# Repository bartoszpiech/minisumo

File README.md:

# minisumo
A minisumo project for my mobile robots classes

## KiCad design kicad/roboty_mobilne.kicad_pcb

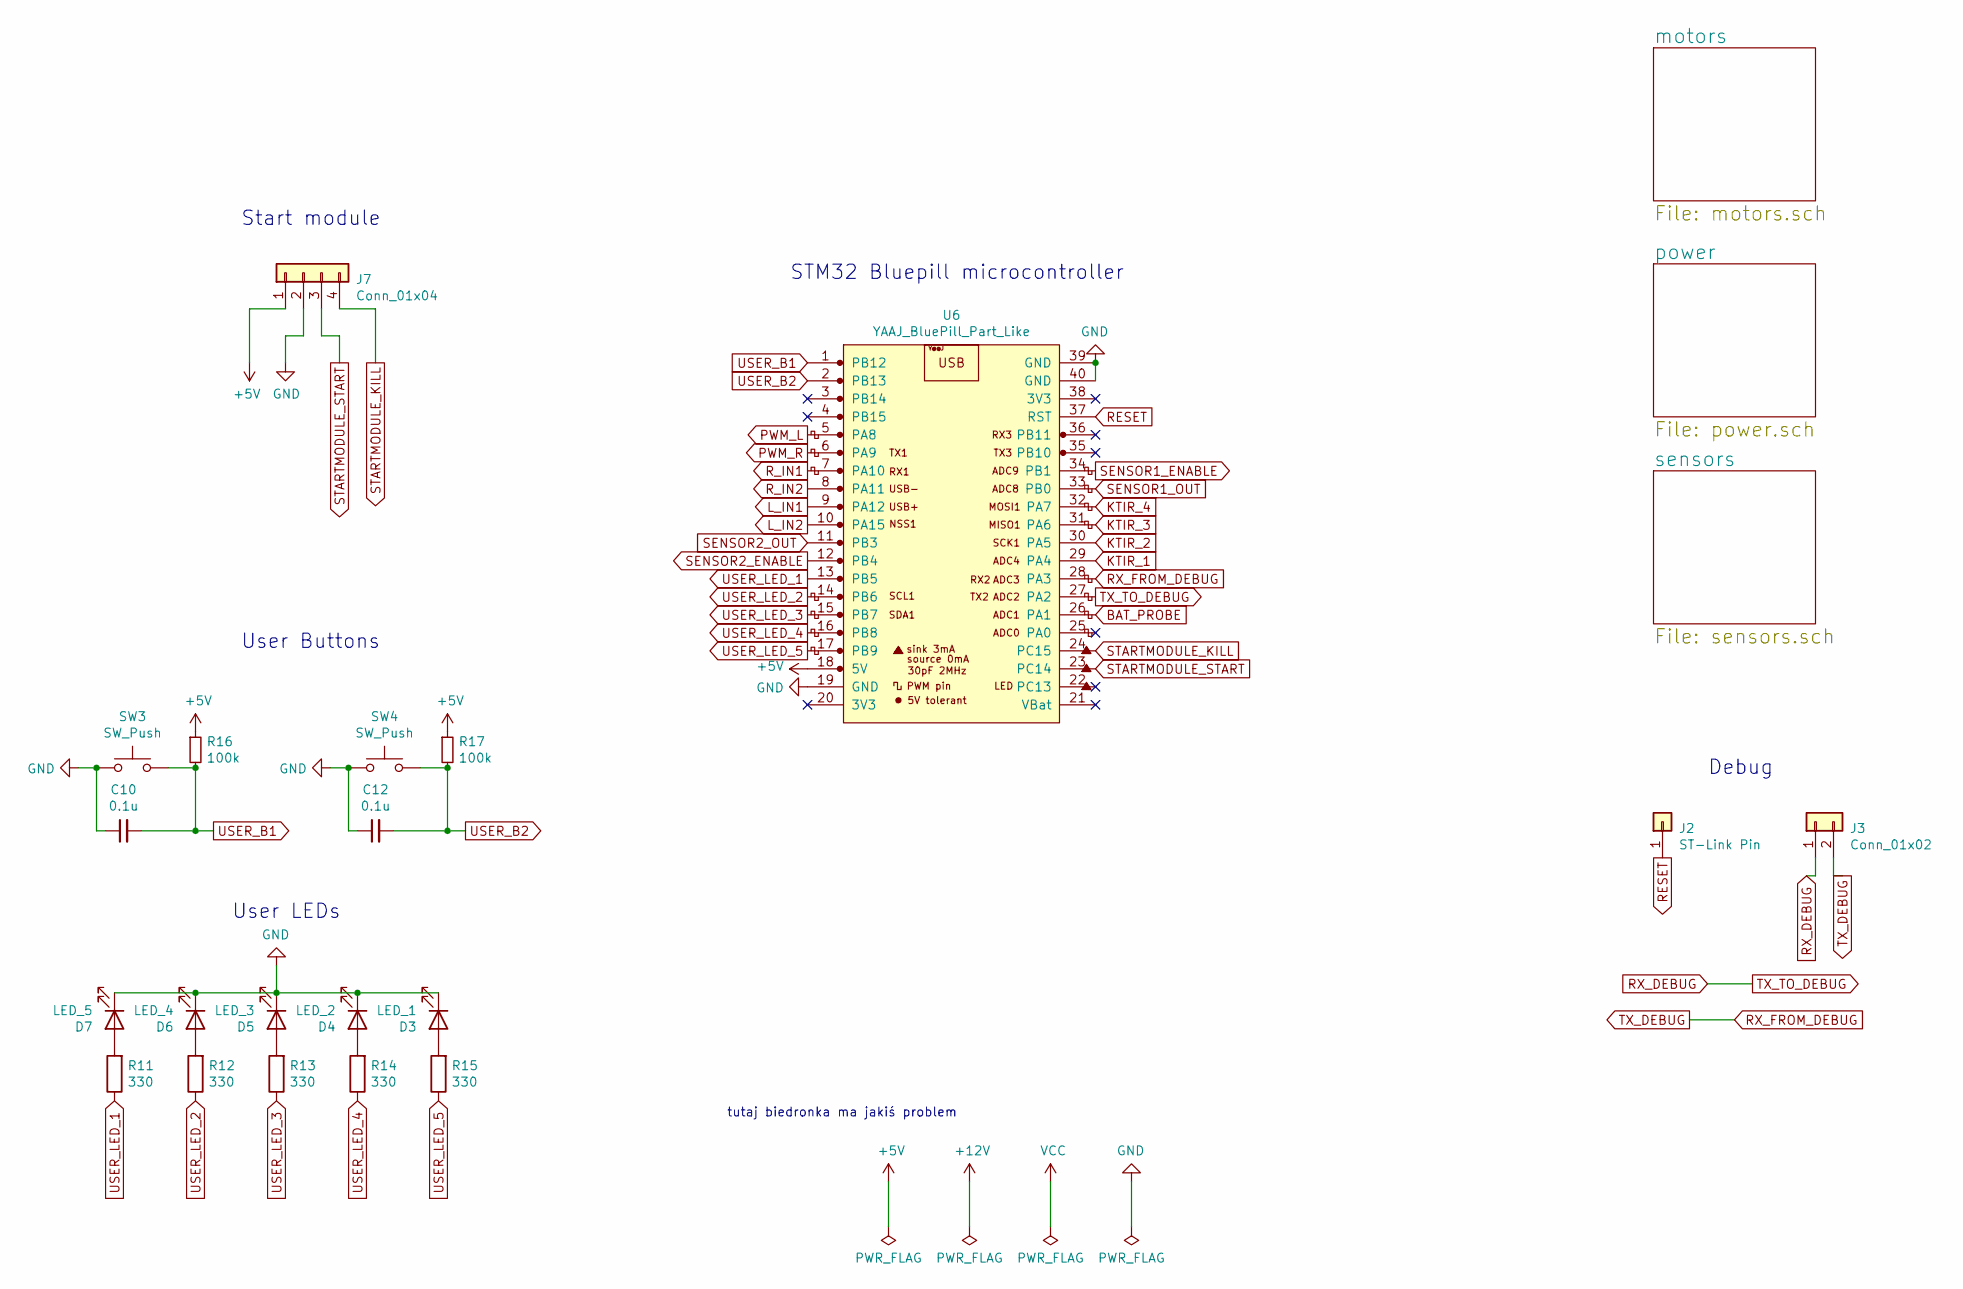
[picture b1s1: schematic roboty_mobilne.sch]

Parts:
C10, C12: 0.1u; C_Disc_D10.5mm_W5.0mm_P7.50mm
D3: LED_1; LED_D5.0mm
D4: LED_2; LED_D5.0mm
D5: LED_3; LED_D5.0mm
D6: LED_4; LED_D5.0mm
D7: LED_5; LED_D5.0mm
J2: ST-Link Pin; PinSocket_1x01_P2.54mm_Vertical
J3: Conn_01x02; PinSocket_1x02_P2.54mm_Vertical
J7: Conn_01x04; PinSocket_1x04_P2.54mm_Vertical
R11, R12, R13, R14, R15: 330; R_1206_3216Metric_Pad1.30x1.75mm_HandSolder
R16, R17: 100k; R_1206_3216Metric_Pad1.30x1.75mm_HandSolder
SW3, SW4: SW_Push; SW_PUSH_6mm_H5mm
U6: YAAJ_BluePill_Part_Like; YAAJ_BluePill_1

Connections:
+5V: J7.1, R16.1, R17.1, U6.18 (5V); also elsewhere on the board
BAT_PROBE: U6.26 (PA1); also elsewhere on the board
GND: C10.1, C12.1, D3.1 (K), D4.1 (K), D5.1 (K), D6.1 (K), D7.1 (K), J7.2, SW3.1, SW4.1, U6.19 (GND), U6.39 (GND), U6.40 (GND); also elsewhere on the board
KTIR_1: U6.29 (PA4); also elsewhere on the board
KTIR_2: U6.30 (PA5); also elsewhere on the board
KTIR_3: U6.31 (PA6); also elsewhere on the board
KTIR_4: U6.32 (PA7); also elsewhere on the board
L_IN1: U6.9 (PA12); also elsewhere on the board
L_IN2: U6.10 (PA15); also elsewhere on the board
unnamed: D3.2 (A), R15.2
unnamed: D4.2 (A), R14.2
unnamed: D5.2 (A), R13.2
unnamed: D6.2 (A), R12.2
unnamed: D7.2 (A), R11.2
PWM_L: U6.5 (PA8); also elsewhere on the board
PWM_R: U6.6 (PA9); also elsewhere on the board
RESET: J2.1, U6.37 (RST)
RX_DEBUG: J3.1, U6.27 (PA2)
RX_FROM_DEBUG: J3.2, U6.28 (PA3)
R_IN1: U6.7 (PA10); also elsewhere on the board
R_IN2: U6.8 (PA11); also elsewhere on the board
SENSOR1_ENABLE: U6.34 (PB1); also elsewhere on the board
SENSOR1_OUT: U6.33 (PB0); also elsewhere on the board
SENSOR2_ENABLE: U6.12 (PB4); also elsewhere on the board
SENSOR2_OUT: U6.11 (PB3); also elsewhere on the board
STARTMODULE_KILL: J7.4, U6.24 (PC15)
STARTMODULE_START: J7.3, U6.23 (PC14)
USER_B1: C10.2, R16.2, SW3.2, U6.1 (PB12)
USER_B2: C12.2, R17.2, SW4.2, U6.2 (PB13)
USER_LED_1: R11.1, U6.13 (PB5)
USER_LED_2: R12.1, U6.14 (PB6)
USER_LED_3: R13.1, U6.15 (PB7)
USER_LED_4: R14.1, U6.16 (PB8)
USER_LED_5: R15.1, U6.17 (PB9)

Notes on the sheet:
User Buttons
User LEDs
STM32 Bluepill microcontroller
Debug
tutaj biedronka ma jakiś problem
Start module

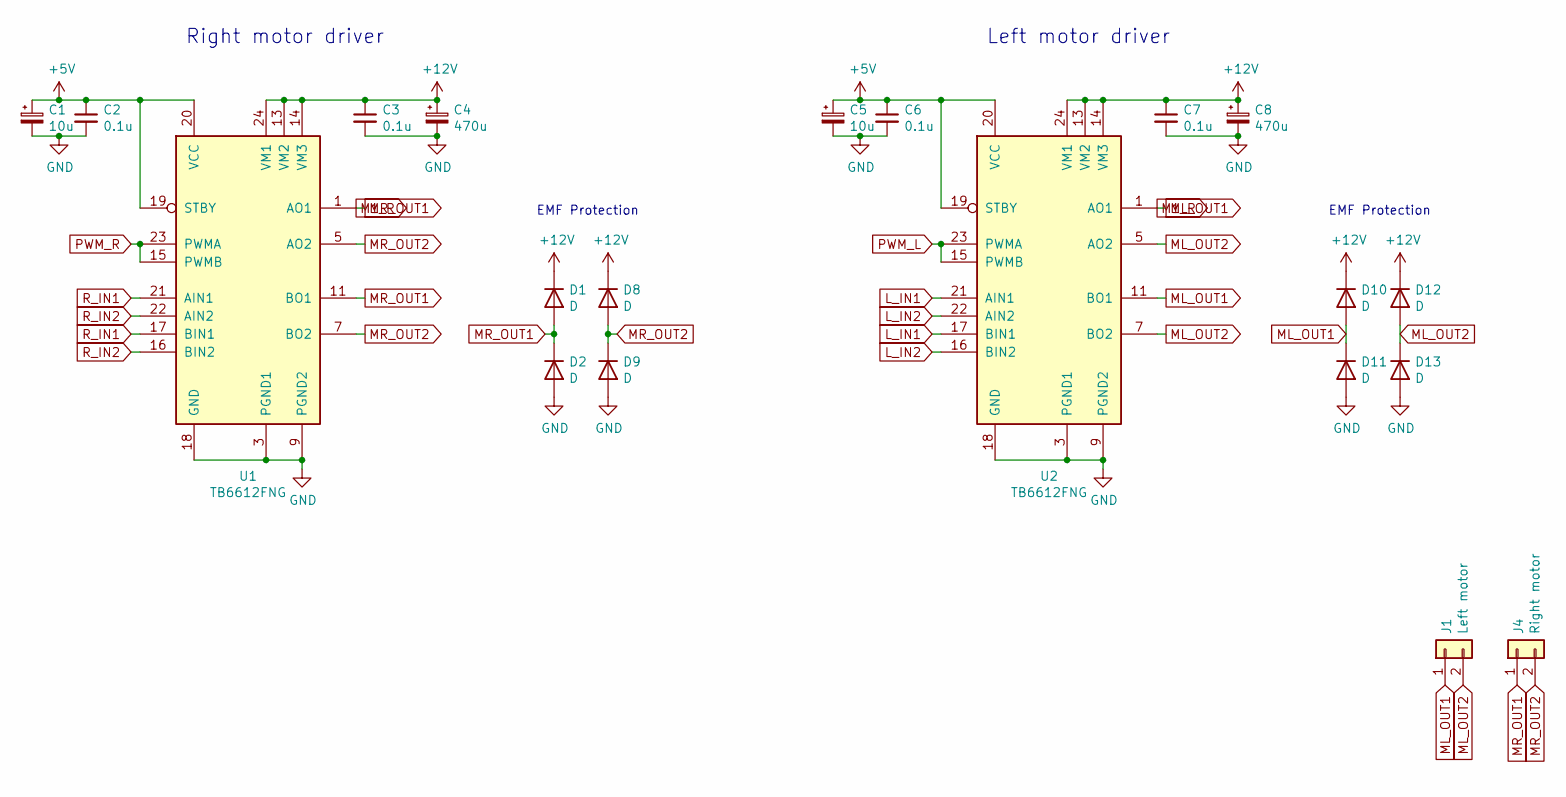
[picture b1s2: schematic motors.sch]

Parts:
C1, C5: 10u; CP_Radial_D5.0mm_P2.00mm
C2, C3, C6, C7: 0.1u; C_Disc_D10.5mm_W5.0mm_P7.50mm
C4, C8: 470u; CP_Radial_D12.5mm_P5.00mm
D1, D2, D8, D9, D10, D11, D12, D13: D; D_DO-41_SOD81_P10.16mm_Horizontal
J1: Left motor; PinSocket_1x02_P2.54mm_Vertical
J4: Right motor; PinSocket_1x02_P2.54mm_Vertical
U1, U2: TB6612FNG; SSOP-24_5.3x8.2mm_P0.65mm

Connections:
+5V: C1.1, C2.1, C5.1, C6.1, U1.19 (STBY), U1.20 (VCC), U2.19 (STBY), U2.20 (VCC); also elsewhere on the board
+12V: C3.1, C4.1, C7.1, C8.1, D1.1 (K), D8.1 (K), D10.1 (K), D12.1 (K), U1.13 (VM2), U1.14 (VM3), U1.24 (VM1), U2.13 (VM2), U2.14 (VM3), U2.24 (VM1); also elsewhere on the board
GND: C1.2, C2.2, C3.2, C4.2, C5.2, C6.2, C7.2, C8.2, D2.2 (A), D9.2 (A), D11.2 (A), D13.2 (A), U1.3 (PGND1), U1.4 (PGND1), U1.9 (PGND2), U1.10 (PGND2), U1.18 (GND), U2.3 (PGND1), U2.4 (PGND1), U2.9 (PGND2), U2.10 (PGND2), U2.18 (GND); also elsewhere on the board
L_IN1: U2.17 (BIN1), U2.21 (AIN1); also elsewhere on the board
L_IN2: U2.16 (BIN2), U2.22 (AIN2); also elsewhere on the board
M1_R: D1.2 (A), D2.1 (K), D10.2 (A), D11.1 (K), J1.1, J4.1, U1.1 (AO1), U1.2 (AO1), U1.11 (BO1), U1.12 (BO1), U2.1 (AO1), U2.2 (AO1), U2.11 (BO1), U2.12 (BO1)
ML_OUT2: D12.2 (A), D13.1 (K), J1.2, U2.5 (AO2), U2.6 (AO2), U2.7 (BO2), U2.8 (BO2)
MR_OUT2: D8.2 (A), D9.1 (K), J4.2, U1.5 (AO2), U1.6 (AO2), U1.7 (BO2), U1.8 (BO2)
PWM_L: U2.15 (PWMB), U2.23 (PWMA); also elsewhere on the board
PWM_R: U1.15 (PWMB), U1.23 (PWMA); also elsewhere on the board
R_IN1: U1.17 (BIN1), U1.21 (AIN1); also elsewhere on the board
R_IN2: U1.16 (BIN2), U1.22 (AIN2); also elsewhere on the board

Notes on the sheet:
Left motor driver
Right motor driver
EMF Protection

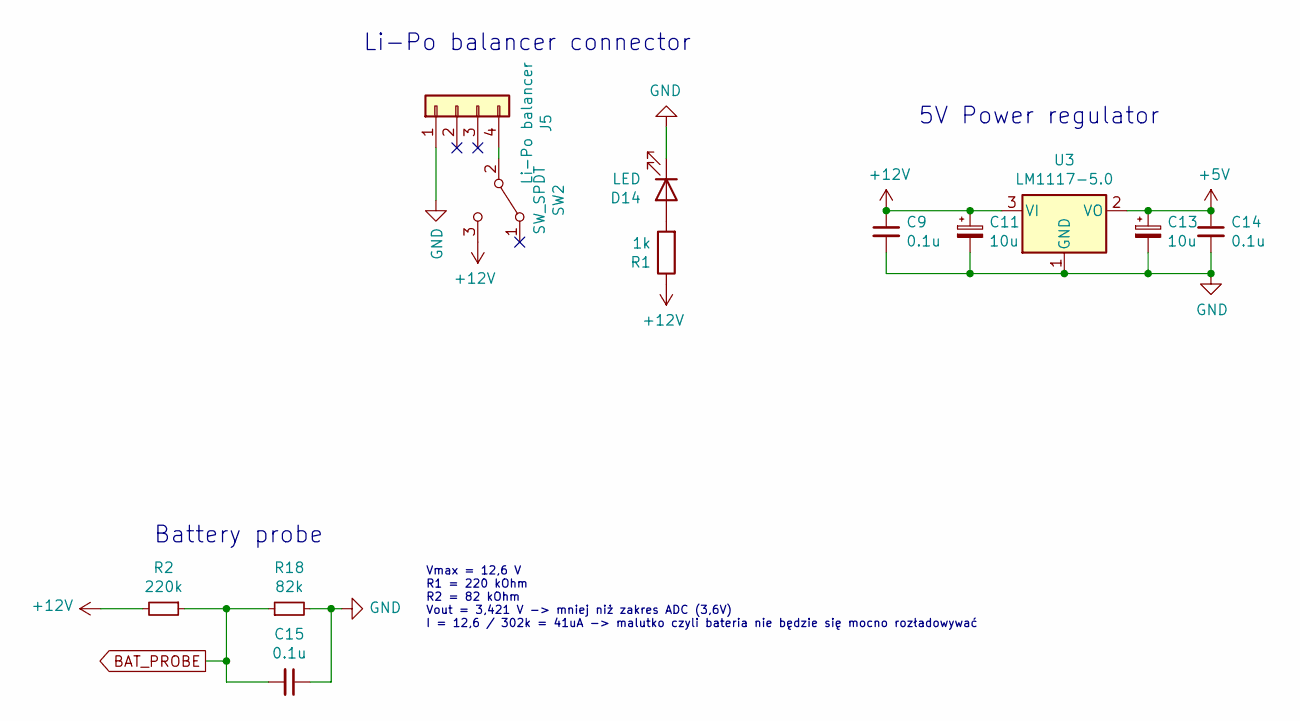
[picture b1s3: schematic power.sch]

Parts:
C9, C14, C15: 0.1u
C11, C13: 10u
D14: LED; LED_D5.0mm
J5: Li-Po balancer; JST_XH_B4B-XH-A_1x04_P2.50mm_Vertical
R1: 1k
R2: 220k
R18: 82k
SW2: SW_SPDT
U3: LM1117-5.0

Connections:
+5V: C13.1, C14.1, U3.2 (VO); also elsewhere on the board
+12V: C9.1, C11.1, R1.1, R2.2, SW2.3 (C), U3.3 (VI); also elsewhere on the board
BAT_PROBE: C15.2, R2.1, R18.1; also elsewhere on the board
GND: C9.2, C11.2, C13.2, C14.2, C15.1, D14.1 (K), J5.1, R18.2, U3.1 (GND); also elsewhere on the board
unnamed: D14.2 (A), R1.2
unnamed: J5.4, SW2.2 (B)

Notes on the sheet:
5V Power regulator
Li-Po balancer connector
Battery probe
Vmax = 12,6 V R1 = 220 kOhm R2 = 82 kOhm Vout = 3,421 V -> mniej niż zakres ADC (3,6V) I = 12,6 / 302k = 41uA -> malutko czyli bateria nie będzie się mocno rozładowywać

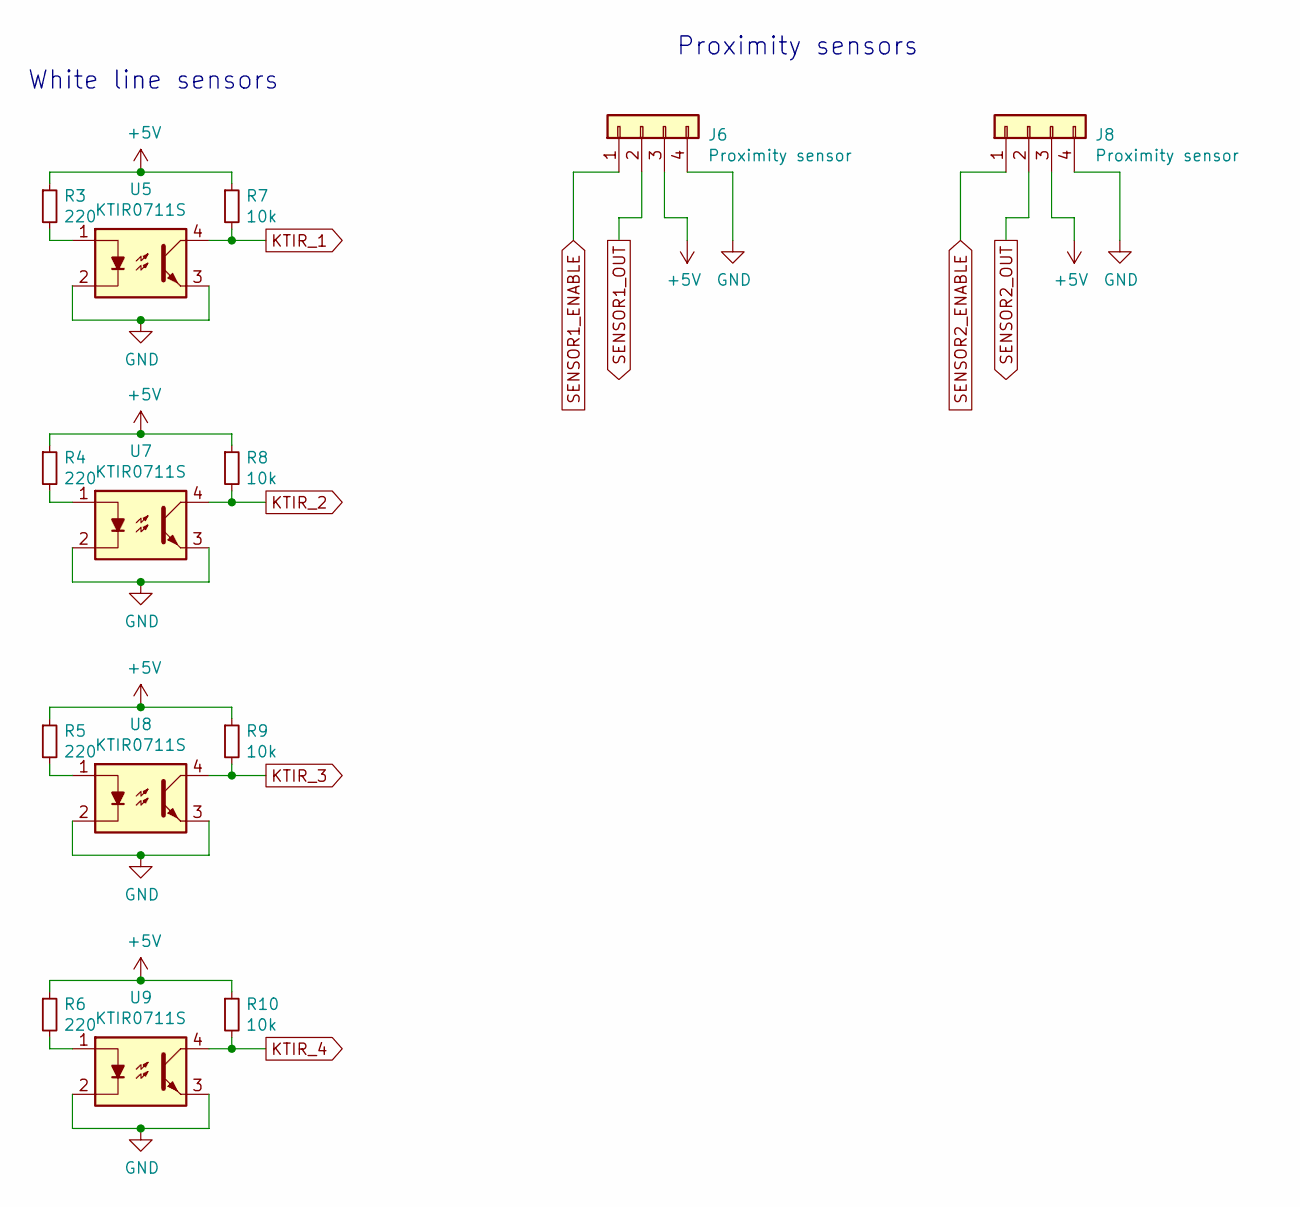
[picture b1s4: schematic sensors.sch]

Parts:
J6, J8: Proximity sensor; PinSocket_1x04_P2.54mm_Vertical
R3, R4, R5, R6: 220
R7, R8, R9, R10: 10k
U5, U7, U8, U9: KTIR0711S

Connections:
+5V: J6.3, J8.3, R3.1, R4.1, R5.1, R6.1, R7.1, R8.1, R9.1, R10.1; also elsewhere on the board
GND: J6.4, J8.4, U5.2, U5.3, U7.2, U7.3, U8.2, U8.3, U9.2, U9.3; also elsewhere on the board
KTIR_1: R7.2, U5.4; also elsewhere on the board
KTIR_2: R8.2, U7.4; also elsewhere on the board
KTIR_3: R9.2, U8.4; also elsewhere on the board
KTIR_4: R10.2, U9.4; also elsewhere on the board
unnamed: R3.2, U5.1
unnamed: R4.2, U7.1
unnamed: R5.2, U8.1
unnamed: R6.2, U9.1
SENSOR1_ENABLE: J6.1; also elsewhere on the board
SENSOR1_OUT: J6.2; also elsewhere on the board
SENSOR2_ENABLE: J8.1; also elsewhere on the board
SENSOR2_OUT: J8.2; also elsewhere on the board

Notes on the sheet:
White line sensors
Proximity sensors

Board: 2 copper layers, 66 parts (12 on the bottom side), 44 nets, no tracks yet.

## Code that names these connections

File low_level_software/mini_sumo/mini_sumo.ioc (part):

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PB13.GPIOParameters=GPIO_Label
Mcu.UserName=STM32F103C8Tx
PC13-TAMPER-RTC.GPIOParameters=GPIO_Label
PA12.GPIOParameters=GPIO_Label
PA9.GPIOParameters=GPIO_Label
PA11.GPIOParameters=GPIO_Label
PA6.GPIO_Label=KTIR3_ADC_IN
PB0.GPIO_Label=SENSOR1_OUT
PB6.GPIO_Label=USER_LED2
PB13.GPIO_Label=USER_B2
PB13.Signal=GPXTI13
PC15-OSC32_OUT.GPIO_Label=STARTMODULE_KILL
RCC.SYSCLKSource=RCC_SYSCLKSOURCE_PLLCLK
PB5.GPIOParameters=GPIO_Label
PD1-OSC_OUT.Signal=RCC_OSC_OUT
PB4.GPIOParameters=GPIO_Label
PA12.Signal=GPIO_Output
PB6.Signal=GPIO_Output
PA8.GPIOParameters=GPIO_Label
PB12.GPIO_Label=USER_B1
PB0.GPIOParameters=GPIO_PuPd,GPIO_Label
PA1.GPIOParameters=GPIO_Label
PB1.GPIO_Label=SENSOR1_ENABLE
PA10.GPIO_Label=R_IN1
PB3.GPIOParameters=GPIO_Label
PB7.Signal=GPIO_Output
PA8.Signal=S_TIM1_CH1
PB6.GPIOParameters=GPIO_Label
PC14-OSC32_IN.GPIOParameters=GPIO_Label
PA13.GPIOParameters=GPIO_Label
PB7.GPIO_Label=USER_LED3
Mcu.Package=LQFP48
PB9.Signal=GPIO_Output
PB1.Signal=GPIO_Output
PA6.Signal=ADCx_IN6
PA10.Signal=GPIO_Output
PA5.GPIOParameters=GPIO_Label
PB5.GPIO_Label=USER_LED1
PC14-OSC32_IN.GPIO_Label=STARTMODULE_START
PC15-OSC32_OUT.GPIOParameters=GPIO_Label
PA4.GPIO_Label=KTIR1_ADC_IN
PB4.Signal=GPIO_Output
PA3.Signal=USART2_RX
PB3.GPIO_Label=SENSOR2_OUT
PA6.GPIOParameters=GPIO_Label
PB8.GPIOParameters=GPIO_Label
PD1-OSC_OUT.Mode=HSE-External-Oscillator
PB9.GPIO_Label=USER_LED5
PA9.GPIO_Label=PWM_L
PC13-TAMPER-RTC.Signal=GPIO_Output
PA11.GPIO_Label=R_IN2
PD0-OSC_IN.Signal=RCC_OSC_IN
PC14-OSC32_IN.Signal=GPXTI14
PA12.GPIO_Label=L_IN1
PB9.GPIOParameters=GPIO_Label
PA3.Mode=Asynchronous
PA13.Signal=GPIO_Output
PB8.GPIO_Label=USER_LED4
PA8.GPIO_Label=PWM_R
PB7.GPIOParameters=GPIO_Label
PA9.Signal=S_TIM1_CH2
PC15-OSC32_OUT.Signal=GPXTI15
PA1.Signal=ADCx_IN1
PD0-OSC_IN.Mode=HSE-External-Oscillator
PA5.Signal=ADCx_IN5
board=custom
PC13-TAMPER-RTC.GPIO_Label=BOARD_LED
PB4.GPIO_Label=SENSOR2_ENABLE
PA1.GPIO_Label=BAT_PROBE_ADC_IN
PA10.GPIOParameters=GPIO_Label
PA4.GPIOParameters=GPIO_Label
Mcu.Name=STM32F103C(8-B)Tx
PA2.Signal=USART2_TX
PA13.GPIO_Label=L_IN2
PB3.Signal=GPXTI3
PA4.Signal=ADCx_IN4
RCC.SYSCLKFreq_VALUE=72000000
PB5.Signal=GPIO_Output
PA7.GPIO_Label=KTIR4_ADC_IN
PA5.GPIO_Label=KTIR2_ADC_IN
PA11.Signal=GPIO_Output
PA2.Mode=Asynchronous
PB8.Signal=GPIO_Output
PB0.Signal=GPIO_Input
PA7.GPIOParameters=GPIO_Label
PB12.GPIOParameters=GPIO_Label
PB12.Signal=GPXTI12
PB0.GPIO_PuPd=GPIO_PULLUP
PB1.GPIOParameters=GPIO_Label
PA7.Signal=ADCx_IN7

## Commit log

2021-05-05 added docs
2021-05-26 modified motors
2021-05-26 modified capacitors and cleaned up
2021-05-27 modified capacitors near h bridge from 10u to 22u
2021-05-27 updated ladybug errors
2021-06-06 fixed diodes, h bridge and modified power supply
2021-06-06 added uC soft
2021-06-06 deleted 3.3V and modified everything to use 5V instead
2021-06-15 created pcb view
